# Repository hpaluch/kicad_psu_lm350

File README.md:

# 3A PSU with LM350

Project goal: Stabilized PSU with LM350 up to 3A and 33V output.

Created first prototype:
- file: [outputs/pcbway/lm350r0-pcbway.zip](outputs/pcbway/lm350r0-pcbway.zip)
- ordered on: https://www.pcbway.com/
- parameters:
  - 2 layers
  - 83.8 x 149.9 mm
  - thickness 1.6mm
  - Green mask

NOTE: Did not verified my prototype yet (planned around end of Dec 2023)

# Required software

KiCad 7, tested 7.0.8 under Windows 10

# Used parts

* LM350:
  - https://www.ti.com/lit/ds/symlink/lm350-n.pdf
  - https://www.hadex.cz/e643-lm350t-stabil12-33v3a-to220/
* 1N4007
  - https://www.tme.eu/Document/9313dc134fe45a55e51de6687beaf874/1n4001.pdf
  - https://www.hadex.cz/a045-1n4007-dioda-uni-1000v1a-do41/ 
* 1N5408
  - https://www.tme.eu/Document/04ec94aa0cc569e9a90a2bc04c8e62a4/1n5400_ser.pdf
  - https://www.hadex.cz/a041-1n5408-dioda-uni-1000v3a-do201/
* CAP polarized 2200uF/63V (2 pieces)
  - https://www.hadex.cz/i645-2200u63v-105-18x36x75mm-elektrolytkondenzator-radialni/
* CAP polarized 10uF/50V
  - https://www.hadex.cz/i870-10u50v-105-5x11x2mm-elektrolytkondenzator-radialni/
* CAP polarized 100uF/50V
  - https://www.hadex.cz/i874-100u50v-105-8x16x35mm-elektrolytkondenzator-radialni/
* Fuse holder PTF 60 for fuse 5x20mm (2pcs)
  - https://www.tme.eu/Document/a0fa896c2198407c3123a251856f56b8/PTF60.pdf
  - https://www.hadex.cz/k730f-pojistkovy-drzak-ptf-60-do-dps-pro-pojistku-5x20mm/
* Fuse 3A 5x20mm
  - https://www.hadex.cz/k817-pojistka-trubickova-5x20-f-315a/
* TODO: other parts

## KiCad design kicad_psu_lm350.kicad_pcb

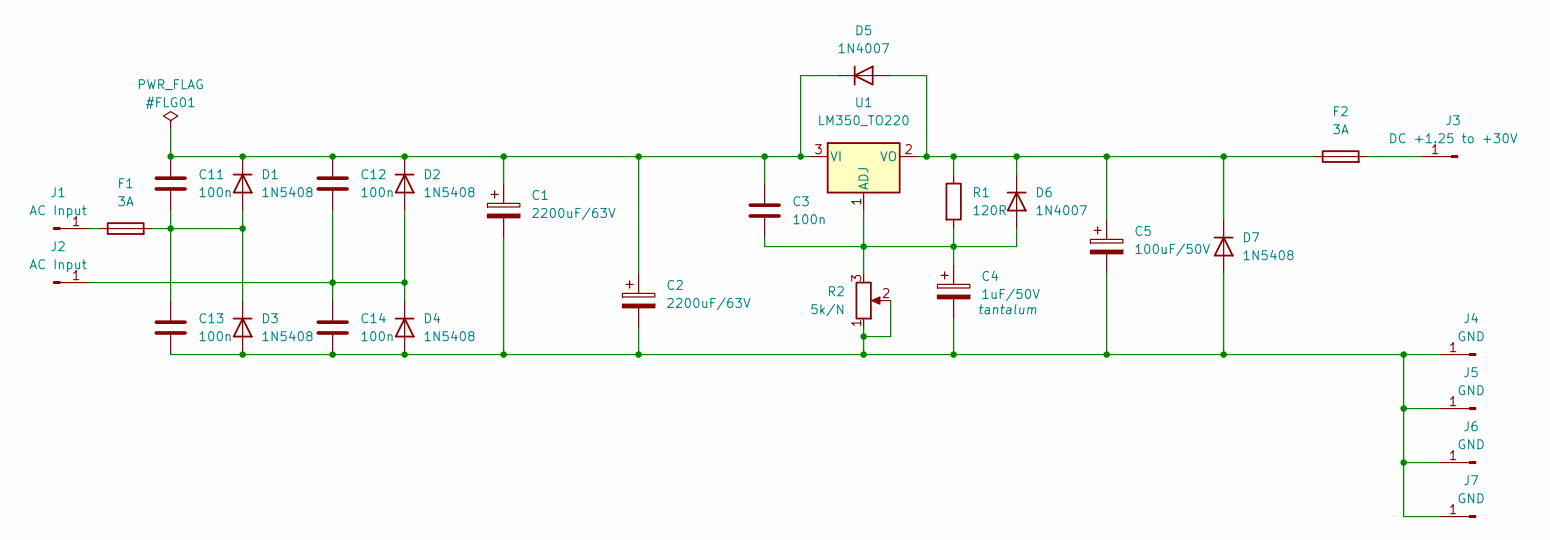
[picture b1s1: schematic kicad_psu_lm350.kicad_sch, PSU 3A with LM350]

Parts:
C1, C2: 2200uF/63V; CP_Radial_D18.0mm_P7.50mm
C3, C11, C12, C13, C14: 100n; C_Disc_D8.0mm_W5.0mm_P5.00mm
C4: 1uF/50V; CP_Radial_D5.0mm_P2.50mm
C5: 100uF/50V; CP_Radial_D8.0mm_P3.50mm
D1, D2, D3, D4, D7: 1N5408; D_DO-201AD_P15.24mm_Horizontal
D5, D6: 1N4007; D_DO-41_SOD81_P10.16mm_Horizontal
F1, F2: 3A; Fuseholder_Cylinder-5x20mm_Schurter_0031_8201_Horizontal_Op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
J1, J2: AC Input; PinSocket_1x01_P2.54mm_Vertical
J3: DC +1.25 to +30V; PinSocket_1x01_P2.54mm_Vertical
J4, J5, J6, J7: GND; PinSocket_1x01_P2.54mm_Vertical
R1: 120R; R_Axial_DIN0207_L6.3mm_D2.5mm_P10.16mm_Horizontal
R2: 5k/N; Potentiometer_Vishay_148-149_Single_Horizontal
U1: LM350_TO220; TO-220-3_Vertical

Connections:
unnamed: C1.1, C2.1, C3.1, C11.1, C12.1, D1.1 (K), D2.1 (K), D5.1 (K), U1.3 (VI)
unnamed: C1.2, C2.2, C4.2, C5.2, C13.2, C14.2, D3.2 (A), D4.2 (A), D7.2 (A), J4.1, J5.1, J6.1, J7.1, R2.1, R2.2
unnamed: C3.2, C4.1, D6.2 (A), R1.2, R2.3, U1.1 (ADJ)
unnamed: C5.1, D5.2 (A), D6.1 (K), D7.1 (K), F2.1, R1.1, U1.2 (VO)
unnamed: C11.2, C13.1, D1.2 (A), D3.1 (K), F1.2
unnamed: C12.2, C14.1, D2.2 (A), D4.1 (K), J2.1
unnamed: F1.1, J1.1
unnamed: F2.2, J3.1

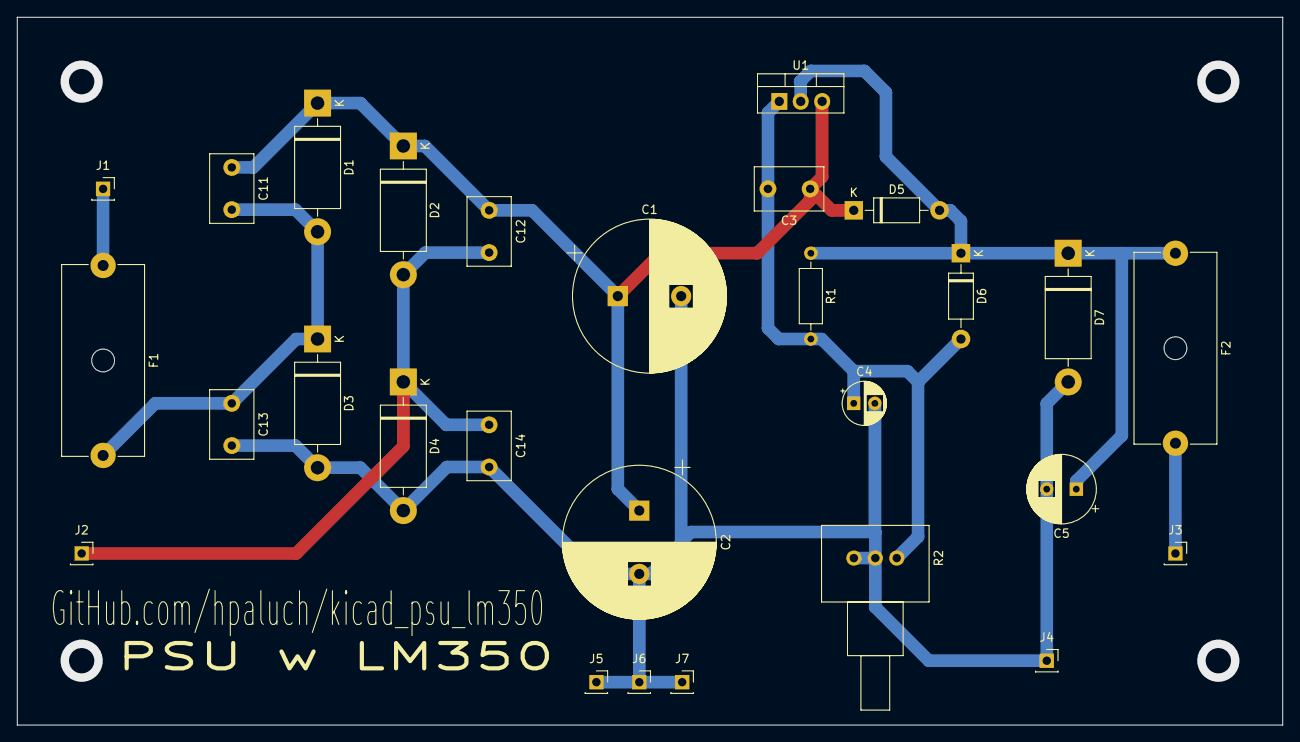
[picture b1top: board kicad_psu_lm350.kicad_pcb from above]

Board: 2 copper layers, 149.9 x 83.8 mm, 28 parts (0 on the bottom side), 8 nets.

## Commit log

2022-12-29 Initial commit - just schematic
2022-12-29 Early footprint assignment
2022-12-29 Early PCB placement
2022-12-30 Swapped pot pins, aligned schematic nets
2022-12-30 C4 should be tantalum to filter HF noise
2023-10-28 Upgraded to KiCad7, board outline, mounting holes
2023-10-28 Requires KiCad 7
2023-10-28 First routed version
2023-11-06 Created prototype - manufactured on pcbway.com
